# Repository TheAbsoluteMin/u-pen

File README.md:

# uPen v2
A Bluetooth smart pen that transforms handwritten notes into digital text.

## Introduction
uPen v2 (the latest version) is a complete redesign of v1. Not only were the PCB and CAD updated but the pen's purpose also changed.

With a sensor PCB and a pen ink refill in a slim case, uPen aims to bridge the gap between handwritten notes and digital notes. Especially when taking notes at school (or anywhere) by hand, it can be tedious to back up those notes online or turn them into online study aids (like Quizlet!). By seamlessly capturing, digitizing, and store handwriting strokes that can be synced online via Bluetooth, uPen v2 avoids cameras and keyboards without requiring any more effort when you write.

## Features
1. NRF52840 MCU
2. 8 megabyte SPI NOR Flash memory IC
3. Bluetooth data syncing
4. CP2102N USB-C coding
5. OLED display
6. USB-C and QVAR sensing USBLC6-2SC6 ESD protection
7. LSM6DSV16XTR IMU
8. Power timing and regulation between 5V USB-C and 3.7V LiPo battery
9. Built-in charging
10. Character recognition

## Schematics

## PCB
uPen v2 was designed with EasyEDA Pro.

### PCB Layers
Top Layer

Inner Layer 1

Inner Layer 2

Bottom Layer

### PCB Assembly
** _Please note that the SDA/SCL lines for the OLED are intentionally not connected on the PCB by default_ **
1. Solder 30 AWG wires for the OLED's SDA/SCL lines to the respective vias as marked on the PCB.
2. Solder on the OLED screen on the back of the PCB.
3. With a JST SH 1.0mm pitch connector, plug in the battery (recommended is 301020 size with 80 mAh).

## CAD Case
3D model [link](https://cad.onshape.com/documents/3034b127fe9271adab18443b/w/723b7faf19a316a6d53fa867/e/b16e1a12b2835dfae5f24d19?renderMode=0&uiState=6aef887ea209f9e2942180de).

Before, uPen v1's case was 18mm wide (that's a really big pen!), and it was designed with Autodesk Fusion.

Now, uPen v2's case is a sleek 12.5mm wide, and it was designed with Onshape.

<details>
<summary>
  <h3>Pictures</h3>
</summary>

</details>

### CAD Case Assembly
1. Attach the Button and Switch extensions on the PCB.
2. After placing the PCB inside the Bottom Case, snap the Top Case above it.
3. With the pen ink refill inside, press the Nose part onto the case. 

## How To Use
1. Ensure uPen's battery is full by charging it with a USB-C cable.
2. Begin writing with uPen v2 as if it's a normal pen.
3. You can view your notes on the screen or sync them online via Bluetooth.

## Firmware Logic: How It Works
1. uPen automatically detects when you start writing.

2. The LSM6DSV16XTR IMU captures handwriting strokes for each character that you write.

3. Each character is separated in the firmware by sensing differences in electrostatic measurements of the QVAR function of the IMU.

4. Characters are translated into text.

5. Notes are stored into the flash memory chip for long term memory.

6. Notes can be transfered via Bluetooth.

### Firmware Setup
1. Flash Nordic's software and bootloader via an SWD programmer onto the NRF52840 MCU. Instructions are found [here](https://www.nordicsemi.com/Products/nRF52840/GetStarted).
2. Upload uPen's main code [here](https://github.com/TheAbsoluteMin/u-pen/blob/main/v2_LATEST/v2_Firmware/src/main.cpp) via USB-C.

## PCB Components BOM

| Part Name | Mfr. | Description | LCSC# | Min Order Qty. | Order Qty. | Unit Price (USD) | Ext.Price (USD) | Product Link |
| :--- | :--- | :--- | :--- | :---: | :---: | :---: | :---: | :--- |
| LQP03TG2N2B02D | muRata | 450mA 2.2nH 250mΩ Thick Film Inductor 0201 Fixed Inductors RoHS | C86107 | 100 | 100 | 0.0014 | 0.14 | [Link](https://www.lcsc.com/product-detail/C86107.html?spm=wm.mxq.bom.0.xh___wm.bjg.btn.cre&lcsc_vid=EwQKVldeTwdaXlNURANeBldeElULUwdSQ1UIXlAFQAcxVlNfQ1deVFBVTlZWUzsOAxUeFF5JWA4dDxMKFgNABAsLWA%3D%3D) |
| X201632MKB4SI | YXC Crystal Oscillators | Crystal 32MHz ±10ppm 8pF SMD2016-4P | C718072 | 5 | 5 | 0.0887 | 0.44 | [Link](https://www.lcsc.com/product-detail/C718072.html?spm=wm.mxq.bom.1.xh___wm.bjg.btn.cre&lcsc_vid=EwQKVldeTwdaXlNURANeBldeElULUwdSQ1UIXlAFQAcxVlNfQ1deVFBVTlZWUzsOAxUeFF5JWA4dDxMKFgNABAsLWA%3D%3D) |
| X1A0000610008 | EPSON | Crystal 32.768kHz ±20ppm 9pF 90kΩ SMD2012-2P | C96341 | 5 | 5 | 0.1908 | 0.95 | [Link](https://www.lcsc.com/product-detail/C96341.html?spm=wm.mxq.bom.2.xh___wm.bjg.btn.cre&lcsc_vid=EwQKVldeTwdaXlNURANeBldeElULUwdSQ1UIXlAFQAcxVlNfQ1deVFBVTlZWUzsOAxUeFF5JWA4dDxMKFgNABAsLWA%3D%3D) |
| NRF52840-QFAA-F-R7 | NORDIC | IC RF TXRX 802.15.4 Bluetooth QFN-48(6x6) | C3606653 | 1 | 1 | 4.8639 | 4.86 | [Link](https://www.lcsc.com/product-detail/C3606653.html?spm=wm.mxq.bom.3.xh___wm.bjg.btn.cre&lcsc_vid=EwQKVldeTwdaXlNURANeBldeElULUwdSQ1UIXlAFQAcxVlNfQ1deVFBVTlZWUzsOAxUeFF5JWA4dDxMKFgNABAsLWA%3D%3D) |
| LQP03TN4N7H02D | muRata | 350mA 4.7nH ±3% 400mΩ 0201 Fixed Inductors RoHS | C86126 | 50 | 50 | 0.0044 | 0.22 | [Link](https://www.lcsc.com/product-detail/C86126.html?spm=wm.mxq.bom.4.xh___wm.bjg.btn.cre&lcsc_vid=EwQKVldeTwdaXlNURANeBldeElULUwdSQ1UIXlAFQAcxVlNfQ1deVFBVTlZWUzsOAxUeFF5JWA4dDxMKFgNABAsLWA%3D%3D) |
| LQG15HS15NJ02D | muRata | 450mA 15nH ±5% 320mΩ 0402 Fixed Inductors RoHS | C86059 | 20 | 20 | 0.0136 | 0.27 | [Link](https://www.lcsc.com/product-detail/C86059.html?spm=wm.mxq.bom.5.xh___wm.bjg.btn.cre&lcsc_vid=EwQKVldeTwdaXlNURANeBldeElULUwdSQ1UIXlAFQAcxVlNfQ1deVFBVTlZWUzsOAxUeFF5JWA4dDxMKFgNABAsLWA%3D%3D) |
| CC0201FRNPO9BN120 | YAGEO | 12pF ±1% 50V Ceramic Capacitor NP0 0201 | C526929 | 100 | 100 | 0.0020 | 0.20 | [Link](https://www.lcsc.com/product-detail/C526929.html?spm=wm.mxq.bom.6.xh___wm.bjg.btn.cre&lcsc_vid=EwQKVldeTwdaXlNURANeBldeElULUwdSQ1UIXlAFQAcxVlNfQ1deVFBVTlZWUzsOAxUeFF5JWA4dDxMKFgNABAsLWA%3D%3D) |
| CC0201BRNPO9BN1R0 | YAGEO | 1pF 50V Ceramic Capacitor NP0 0201 | C281747 | 100 | 100 | 0.0014 | 0.14 | [Link](https://www.lcsc.com/product-detail/C281747.html?spm=wm.mxq.bom.7.xh___wm.bjg.btn.cre&lcsc_vid=EwQKVldeTwdaXlNURANeBldeElULUwdSQ1UIXlAFQAcxVlNfQ1deVFBVTlZWUzsOAxUeFF5JWA4dDxMKFgNABAsLWA%3D%3D) |
| CC0201BRNPO9BN1R2 | YAGEO | 1.2pF 50V Ceramic Capacitor NP0 0201 | C326704 | 100 | 100 | 0.0013 | 0.13 | [Link](https://www.lcsc.com/product-detail/C326704.html?spm=wm.mxq.bom.8.xh___wm.bjg.btn.cre&lcsc_vid=EwQKVldeTwdaXlNURANeBldeElULUwdSQ1UIXlAFQAcxVlNfQ1deVFBVTlZWUzsOAxUeFF5JWA4dDxMKFgNABAsLWA%3D%3D) |
| CL03A104KP3NNNC | Samsung Electro-Mechanics | 100nF ±10% 10V Ceramic Capacitor X5R 0201 | C49062 | 100 | 100 | 0.0012 | 0.12 | [Link](https://www.lcsc.com/product-detail/C49062.html?spm=wm.mxq.bom.9.xh___wm.bjg.btn.cre&lcsc_vid=EwQKVldeTwdaXlNURANeBldeElULUwdSQ1UIXlAFQAcxVlNfQ1deVFBVTlZWUzsOAxUeFF5JWA4dDxMKFgNABAsLWA%3D%3D) |
| CC0201GRNPO9BN101 | YAGEO | 100pF ±2% 50V Ceramic Capacitor NP0 0201 | C541242 | 100 | 100 | 0.0017 | 0.17 | [Link](https://www.lcsc.com/product-detail/C541242.html?spm=wm.mxq.bom.10.xh___wm.bjg.btn.cre&lcsc_vid=EwQKVldeTwdaXlNURANeBldeElULUwdSQ1UIXlAFQAcxVlNfQ1deVFBVTlZWUzsOAxUeFF5JWA4dDxMKFgNABAsLWA%3D%3D) |
| GRM155R61A105KE15D | muRata | 1uF ±10% 10V Ceramic Capacitor X5R 0402 | C76999 | 50 | 50 | 0.0029 | 0.15 | [Link](https://www.lcsc.com/product-detail/C76999.html?spm=wm.mxq.bom.11.xh___wm.bjg.btn.cre&lcsc_vid=EwQKVldeTwdaXlNURANeBldeElULUwdSQ1UIXlAFQAcxVlNfQ1deVFBVTlZWUzsOAxUeFF5JWA4dDxMKFgNABAsLWA%3D%3D) |
| CC0201KRX5R7BB473 | YAGEO | 47nF ±10% 16V Ceramic Capacitor X5R 0201 | C505465 | 100 | 100 | 0.0021 | 0.21 | [Link](https://www.lcsc.com/product-detail/C505465.html?spm=wm.mxq.bom.12.xh___wm.bjg.btn.cre&lcsc_vid=EwQKVldeTwdaXlNURANeBldeElULUwdSQ1UIXlAFQAcxVlNfQ1deVFBVTlZWUzsOAxUeFF5JWA4dDxMKFgNABAsLWA%3D%3D) |
| AF0201FR-0710KL | YAGEO | 50mW 10kΩ 25V Thick Film Resistor ±1% ±200ppm/°C 0201 Chip Resistor - Surface Mount RoHS | C143978 | 100 | 100 | 0.0019 | 0.19 | [Link](https://www.lcsc.com/product-detail/C143978.html?spm=wm.mxq.bom.13.xh___wm.bjg.btn.cre&lcsc_vid=EwQKVldeTwdaXlNURANeBldeElULUwdSQ1UIXlAFQAcxVlNfQ1deVFBVTlZWUzsOAxUeFF5JWA4dDxMKFgNABAsLWA%3D%3D) |
| GD25Q64CWIGR | GigaDevice Semicon Beijing | 64Mbit 2.7V~3.6V 120MHz SPI WSON-8-EP(5x6) Memory RoHS | C395511 | 1 | 1 | 1.0200 | 1.02 | [Link](https://www.lcsc.com/product-detail/C395511.html?spm=wm.mxq.bom.14.xh___wm.bjg.btn.cre&lcsc_vid=EwQKVldeTwdaXlNURANeBldeElULUwdSQ1UIXlAFQAcxVlNfQ1deVFBVTlZWUzsOAxUeFF5JWA4dDxMKFgNABAsLWA%3D%3D) |
| WR02X4702FAL | Walsin | 47kΩ ±1% 50mW 0201 Thick Film Resistor | C171928 | 100 | 100 | 0.0005 | 0.05 | [Link](https://www.lcsc.com/product-detail/C171928.html?spm=wm.mxq.bom.15.xh___wm.bjg.btn.cre&lcsc_vid=EwQKVldeTwdaXlNURANeBldeElULUwdSQ1UIXlAFQAcxVlNfQ1deVFBVTlZWUzsOAxUeFF5JWA4dDxMKFgNABAsLWA%3D%3D) |
| LQM18DN100M70L | muRata | 300mA 10uH ±20% 100mA 1.365Ω 0603 Fixed Inductors RoHS | C713281 | 5 | 5 | 0.0850 | 0.43 | [Link](https://www.lcsc.com/product-detail/C713281.html?spm=wm.mxq.bom.16.xh___wm.bjg.btn.cre&lcsc_vid=EwQKVldeTwdaXlNURANeBldeElULUwdSQ1UIXlAFQAcxVlNfQ1deVFBVTlZWUzsOAxUeFF5JWA4dDxMKFgNABAsLWA%3D%3D) |
| EVQP2P02W | PANASONIC | Tactile Switch SPST 1N 2.5mm J-Lead 4.7mm x 3.5mm Surface Mount | C512395 | 1 | 2 | 0.3696 | 0.74 | [Link](https://www.lcsc.com/product-detail/C512395.html?spm=wm.mxq.bom.17.xh___wm.bjg.btn.cre&lcsc_vid=EwQKVldeTwdaXlNURANeBldeElULUwdSQ1UIXlAFQAcxVlNfQ1deVFBVTlZWUzsOAxUeFF5JWA4dDxMKFgNABAsLWA%3D%3D) |
| AMCA31-2R450G-S1F-T3 | ABRACON | Surface Mount WLAN / Bluetooth Chip Antenna | C3283994 | 5 | 5 | 0.2603 | 1.30 | [Link](https://www.lcsc.com/product-detail/C3283994.html?spm=wm.mxq.bom.19.xh___wm.bjg.btn.cre&lcsc_vid=EwQKVldeTwdaXlNURANeBldeElULUwdSQ1UIXlAFQAcxVlNfQ1deVFBVTlZWUzsOAxUeFF5JWA4dDxMKFgNABAsLWA%3D%3D) |
| CC0402CRNPO9BN1R5 | YAGEO | 1.5pF 50V Ceramic Capacitor NP0 0402 | C189471 | 100 | 100 | 0.0010 | 0.10 | [Link](https://www.lcsc.com/product-detail/C189471.html?spm=wm.mxq.bom.20.xh___wm.bjg.btn.cre&lcsc_vid=EwQKVldeTwdaXlNURANeBldeElULUwdSQ1UIXlAFQAcxVlNfQ1deVFBVTlZWUzsOAxUeFF5JWA4dDxMKFgNABAsLWA%3D%3D) |
| MLG1005S3N9BT000 | TDK | 700mA 3.9nH 110mΩ Multilayer inductor 0402 Fixed Inductors RoHS | C76775 | 10 | 10 | 0.0065 | 0.07 | [Link](https://www.lcsc.com/product-detail/C76775.html?spm=wm.mxq.bom.21.xh___wm.bjg.btn.cre&lcsc_vid=EwQKVldeTwdaXlNURANeBldeElULUwdSQ1UIXlAFQAcxVlNfQ1deVFBVTlZWUzsOAxUeFF5JWA4dDxMKFgNABAsLWA%3D%3D) |
| CP2102N-A02-GQFN20R | SILICON LABS | USB to UART 3Mbps QFN-20-EP(3x3) Controllers RoHS | C969913 | 1 | 1 | 1.4298 | 1.43 | [Link](https://www.lcsc.com/product-detail/C969913.html?spm=wm.mxq.bom.22.xh___wm.bjg.btn.cre&lcsc_vid=EwQKVldeTwdaXlNURANeBldeElULUwdSQ1UIXlAFQAcxVlNfQ1deVFBVTlZWUzsOAxUeFF5JWA4dDxMKFgNABAsLWA%3D%3D) |
| TYPE-C16PIN | SHOU HAN | USB-C (USB TYPE-C) Receptacle Connector 16 Position Surface Mount, Right Angle | C393939 | 10 | 10 | 0.0595 | 0.60 | [Link](https://www.lcsc.com/product-detail/C393939.html?spm=wm.mxq.bom.23.xh___wm.bjg.btn.cre&lcsc_vid=EwQKVldeTwdaXlNURANeBldeElULUwdSQ1UIXlAFQAcxVlNfQ1deVFBVTlZWUzsOAxUeFF5JWA4dDxMKFgNABAsLWA%3D%3D) |
| XC6206P332MR-G | TOREX | 3.3V Positive Fixed SOT-23-3L Voltage Regulators - Linear, Low Drop Out (LDO) Regulators RoHS | C5446 | 5 | 5 | 0.1342 | 0.67 | [Link](https://www.lcsc.com/product-detail/C5446.html?spm=wm.mxq.bom.24.xh___wm.bjg.btn.cre&lcsc_vid=EwQKVldeTwdaXlNURANeBldeElULUwdSQ1UIXlAFQAcxVlNfQ1deVFBVTlZWUzsOAxUeFF5JWA4dDxMKFgNABAsLWA%3D%3D) |
| AF0201FR-075K1L | YAGEO | 50mW 5.1kΩ 25V Thick Film Resistor ±1% ±200ppm/°C 0201 Chip Resistor - Surface Mount RoHS | C143995 | 100 | 100 | 0.0019 | 0.19 | [Link](https://www.lcsc.com/product-detail/C143995.html?spm=wm.mxq.bom.25.xh___wm.bjg.btn.cre&lcsc_vid=EwQKVldeTwdaXlNURANeBldeElULUwdSQ1UIXlAFQAcxVlNfQ1deVFBVTlZWUzsOAxUeFF5JWA4dDxMKFgNABAsLWA%3D%3D) |
| CGA0402X5R475K160GT | HRE | 4.7uF X5R ±10% 16V 0402 Ceramic Capacitors | C52037851 | 20 | 20 | 0.0144 | 0.29 | [Link](https://www.lcsc.com/product-detail/C52037851.html?spm=wm.mxq.bom.26.xh___wm.bjg.btn.cre&lcsc_vid=EwQKVldeTwdaXlNURANeBldeElULUwdSQ1UIXlAFQAcxVlNfQ1deVFBVTlZWUzsOAxUeFF5JWA4dDxMKFgNABAsLWA%3D%3D) |
| USBLC6-2SC6 | ST | 17VC Clamp 5A Ipp ESD DIODE SOT-23-6L | C7519 | 5 | 5 | 0.1391 | 0.70 | [Link](https://www.lcsc.com/product-detail/C7519.html?spm=wm.mxq.bom.27.xh___wm.bjg.btn.cre&lcsc_vid=EwQKVldeTwdaXlNURANeBldeElULUwdSQ1UIXlAFQAcxVlNfQ1deVFBVTlZWUzsOAxUeFF5JWA4dDxMKFgNABAsLWA%3D%3D) |
| RC0201FR-0722K1L | YAGEO | 50mW 22.1kΩ 25V Thick Film Resistor ±1% ±200ppm/°C 0201 Chip Resistor - Surface Mount RoHS | C142019 | 100 | 100 | 0.0005 | 0.05 | [Link](https://www.lcsc.com/product-detail/C142019.html?spm=wm.mxq.bom.28.xh___wm.bjg.btn.cre&lcsc_vid=EwQKVldeTwdaXlNURANeBldeElULUwdSQ1UIXlAFQAcxVlNfQ1deVFBVTlZWUzsOAxUeFF5JWA4dDxMKFgNABAsLWA%3D%3D) |
| 0201WMF4752TEE | UNI-ROYAL | 47.5kΩ ±1% 50mW 0201 Thick Film Resistor | C473579 | 100 | 100 | 0.0005 | 0.05 | [Link](https://www.lcsc.com/product-detail/C473579.html?spm=wm.mxq.bom.29.xh___wm.bjg.btn.cre&lcsc_vid=EwQKVldeTwdaXlNURANeBldeElULUwdSQ1UIXlAFQAcxVlNfQ1deVFBVTlZWUzsOAxUeFF5JWA4dDxMKFgNABAsLWA%3D%3D) |
| RC0201FR-0727KL | YAGEO | 27kΩ 50mW 25V Thick Film Resistor ±1% ±200ppm/°C 0201 Chip Resistor - Surface Mount RoHS | C273283 | 100 | 100 | 0.0005 | 0.05 | [Link](https://www.lcsc.com/product-detail/C273283.html?spm=wm.mxq.bom.30.xh___wm.bjg.btn.cre&lcsc_vid=EwQKVldeTwdaXlNURANeBldeElULUwdSQ1UIXlAFQAcxVlNfQ1deVFBVTlZWUzsOAxUeFF5JWA4dDxMKFgNABAsLWA%3D%3D) |
| RC0201JR-071KL | YAGEO | 50mW 1kΩ 25V Thick Film Resistor ±5% ±200ppm/°C 0201 Chip Resistor - Surface Mount RoHS | C131396 | 100 | 100 | 0.0004 | 0.04 | [Link](https://www.lcsc.com/product-detail/C131396.html?spm=wm.mxq.bom.31.xh___wm.bjg.btn.cre&lcsc_vid=EwQKVldeTwdaXlNURANeBldeElULUwdSQ1UIXlAFQAcxVlNfQ1deVFBVTlZWUzsOAxUeFF5JWA4dDxMKFgNABAsLWA%3D%3D) |
| RC0201FR-07100KL | YAGEO | 50mW 100kΩ 25V Thick Film Resistor ±1% ±200ppm/°C 0201 Chip Resistor - Surface Mount RoHS | C106224 | 100 | 100 | 0.0006 | 0.06 | [Link](https://www.lcsc.com/product-detail/C106224.html?spm=wm.mxq.bom.32.xh___wm.bjg.btn.cre&lcsc_vid=EwQKVldeTwdaXlNURANeBldeElULUwdSQ1UIXlAFQAcxVlNfQ1deVFBVTlZWUzsOAxUeFF5JWA4dDxMKFgNABAsLWA%3D%3D) |
| SH1.0mm-2P-WT | LXWCONN | Surface Mount, Right Angle 1mm 1A SH 50V -25°C~+85°C Tin 2P 2 1 1x2P SMD,P=1mm,Surface Mount,Right Angle Headers, Male Pins | C53055318 | 20 | 20 | 0.0225 | 0.45 | [Link](https://www.lcsc.com/product-detail/C53055318.html?spm=wm.mxq.bom.33.xh___wm.bjg.btn.cre&lcsc_vid=EwQKVldeTwdaXlNURANeBldeElULUwdSQ1UIXlAFQAcxVlNfQ1deVFBVTlZWUzsOAxUeFF5JWA4dDxMKFgNABAsLWA%3D%3D) |
| MCP73831T-2ATI/OT | MICROCHIP | 3.75V~6V 1 Lithium Battery 550mA SOT-23-5 Battery Chargers RoHS | C14879 | 1 | 1 | 0.8160 | 0.82 | [Link](https://www.lcsc.com/product-detail/C14879.html?spm=wm.mxq.bom.34.xh___wm.bjg.btn.cre&lcsc_vid=EwQKVldeTwdaXlNURANeBldeElULUwdSQ1UIXlAFQAcxVlNfQ1deVFBVTlZWUzsOAxUeFF5JWA4dDxMKFgNABAsLWA%3D%3D) |
| TPS2116DRLR | TI | 2 Channel 2.5A SOT-583 | C3235557 | 1 | 1 | 0.3234 | 0.32 | [Link](https://www.lcsc.com/product-detail/C3235557.html?spm=wm.mxq.bom.35.xh___wm.bjg.btn.cre&lcsc_vid=EwQKVldeTwdaXlNURANeBldeElULUwdSQ1UIXlAFQAcxVlNfQ1deVFBVTlZWUzsOAxUeFF5JWA4dDxMKFgNABAsLWA%3D%3D) |
| RC0201FR-07620RL | YAGEO | 620Ω 50mW 25V Thick Film Resistor ±1% ±200ppm/°C 0201 Chip Resistor - Surface Mount RoHS | C295811 | 100 | 100 | 0.0005 | 0.05 | [Link](https://www.lcsc.com/product-detail/C295811.html?spm=wm.mxq.bom.36.xh___wm.bjg.btn.cre&lcsc_vid=EwQKVldeTwdaXlNURANeBldeElULUwdSQ1UIXlAFQAcxVlNfQ1deVFBVTlZWUzsOAxUeFF5JWA4dDxMKFgNABAsLWA%3D%3D) |
| KT-0603YG | Hubei KENTO Elec | Yellow Green LED Indication - Discrete 2V~2.2V 0603 | C2289 | 50 | 50 | 0.0066 | 0.33 | [Link](https://www.lcsc.com/product-detail/C2289.html?spm=wm.mxq.bom.37.xh___wm.bjg.btn.cre&lcsc_vid=EwQKVldeTwdaXlNURANeBldeElULUwdSQ1UIXlAFQAcxVlNfQ1deVFBVTlZWUzsOAxUeFF5JWA4dDxMKFgNABAsLWA%3D%3D) |
| HX MSS12C02-BB2.0 | hanxia | Slide Switch SPDT 100mA @ 12V Surface Mount Rectangular Columnar 6.65mm | C25168817 | 5 | 5 | 0.0853 | 0.43 | [Link](https://www.lcsc.com/product-detail/C25168817.html?spm=wm.mxq.bom.38.xh___wm.bjg.btn.cre&lcsc_vid=EwQKVldeTwdaXlNURANeBldeElULUwdSQ1UIXlAFQAcxVlNfQ1deVFBVTlZWUzsOAxUeFF5JWA4dDxMKFgNABAsLWA%3D%3D) |
| LSM6DSV16XTR | ST | LGA-14(2.5x3) IMUs (Inertial Measurement Units) RoHS | C5267406 | 1 | 1 | 2.4405 | 2.44 | [Link](https://www.lcsc.com/product-detail/C5267406.html?spm=wm.mxq.bom.39.xh___wm.bjg.btn.cre&lcsc_vid=EwQKVldeTwdaXlNURANeBldeElULUwdSQ1UIXlAFQAcxVlNfQ1deVFBVTlZWUzsOAxUeFF5JWA4dDxMKFgNABAsLWA%3D%3D) |
| RC0201FR-072K2L | YAGEO | 50mW 2.2kΩ 25V Thick Film Resistor ±1% ±200ppm/°C 0201 Chip Resistor - Surface Mount RoHS | C142018 | 100 | 100 | 0.0005 | 0.05 | [Link](https://www.lcsc.com/product-detail/C142018.html?spm=wm.mxq.bom.40.xh___wm.bjg.btn.cre&lcsc_vid=EwQKVldeTwdaXlNURANeBldeElULUwdSQ1UIXlAFQAcxVlNfQ1deVFBVTlZWUzsOAxUeFF5JWA4dDxMKFgNABAsLWA%3D%3D) |
| X087-2832TSWIG02-H14 | Wisevision | 0.87 128x32 SSD1312 chip I2C LCD, OLED, Graphic RoHS | C18723015 | 1 | 1 | 1.4902 | 1.49 | [Link](https://www.lcsc.com/product-detail/C18723015.html?spm=wm.mxq.bom.41.xh___wm.bjg.btn.cre&lcsc_vid=EwQKVldeTwdaXlNURANeBldeElULUwdSQ1UIXlAFQAcxVlNfQ1deVFBVTlZWUzsOAxUeFF5JWA4dDxMKFgNABAsLWA%3D%3D) |
| CC0603KRX7R7BB225 | YAGEO | 2.2uF ±10% 16V Ceramic Capacitor X7R 0603 | C914769 | 10 | 10 | 0.0381 | 0.38 | [Link](https://www.lcsc.com/product-detail/C914769.html?spm=wm.mxq.bom.42.xh___wm.bjg.btn.cre&lcsc_vid=EwQKVldeTwdaXlNURANeBldeElULUwdSQ1UIXlAFQAcxVlNfQ1deVFBVTlZWUzsOAxUeFF5JWA4dDxMKFgNABAsLWA%3D%3D) |
| CGA0603X7R475K160JT | HRE | 4.7uF ±10% 16V Ceramic Capacitor X7R 0603 | C22399629 | 20 | 20 | 0.0174 | 0.35 | [Link](https://www.lcsc.com/product-detail/C22399629.html?spm=wm.mxq.bom.43.xh___wm.bjg.btn.cre&lcsc_vid=EwQKVldeTwdaXlNURANeBldeElULUwdSQ1UIXlAFQAcxVlNfQ1deVFBVTlZWUzsOAxUeFF5JWA4dDxMKFgNABAsLWA%3D%3D) |
| TCC0201X7R104K160ZT | CCTC | 100nF ±10% 16V Ceramic Capacitor X7R 0201 | C18164586 | 50 | 50 | 0.0017 | 0.09 | [Link](https://www.lcsc.com/product-detail/C18164586.html?spm=wm.mxq.bom.44.xh___wm.bjg.btn.cre&lcsc_vid=EwQKVldeTwdaXlNURANeBldeElULUwdSQ1UIXlAFQAcxVlNfQ1deVFBVTlZWUzsOAxUeFF5JWA4dDxMKFgNABAsLWA%3D%3D) |
| CC0603KRX7R7BB105 | YAGEO | 1uF ±10% 16V Ceramic Capacitor X7R 0603 | C106248 | 50 | 50 | 0.0039 | 0.20 | [Link](https://www.lcsc.com/product-detail/C106248.html?spm=wm.mxq.bom.45.xh___wm.bjg.btn.cre&lcsc_vid=EwQKVldeTwdaXlNURANeBldeElULUwdSQ1UIXlAFQAcxVlNfQ1deVFBVTlZWUzsOAxUeFF5JWA4dDxMKFgNABAsLWA%3D%3D) |
| RC0201FR-07560KL | YAGEO | 50mW 560kΩ 25V Thick Film Resistor ±1% ±200ppm/°C 0201 Chip Resistor - Surface Mount RoHS | C295807 | 100 | 100 | 0.0005 | 0.05 | [Link](https://www.lcsc.com/product-detail/C295807.html?spm=wm.mxq.bom.46.xh___wm.bjg.btn.cre&lcsc_vid=EwQKVldeTwdaXlNURANeBldeElULUwdSQ1UIXlAFQAcxVlNfQ1deVFBVTlZWUzsOAxUeFF5JWA4dDxMKFgNABAsLWA%3D%3D) |
| FDN338P | onsemi | P-Channel 20V 1.6A 0.5W Surface Mount SOT-23 | C24855 | 5 | 5 | 0.1807 | 0.90 | [Link](https://www.lcsc.com/product-detail/C24855.html?spm=wm.mxq.bom.47.xh___wm.bjg.btn.cre&lcsc_vid=EwQKVldeTwdaXlNURANeBldeElULUwdSQ1UIXlAFQAcxVlNfQ1deVFBVTlZWUzsOAxUeFF5JWA4dDxMKFgNABAsLWA%3D%3D) |
| FDN335N | onsemi | N-Channel 20V 1.7A 0.5W Surface Mount SOT-23-3 | C241804 | 5 | 5 | 0.1477 | 0.74 | [Link](https://www.lcsc.com/product-detail/C241804.html?spm=wm.mxq.bom.48.xh___wm.bjg.btn.cre&lcsc_vid=EwQKVldeTwdaXlNURANeBldeElULUwdSQ1UIXlAFQAcxVlNfQ1deVFBVTlZWUzsOAxUeFF5JWA4dDxMKFgNABAsLWA%3D%3D) |
| RC0201FR-071ML | YAGEO | 50mW 1MΩ 25V Thick Film Resistor ±1% ±200ppm/°C 0201 Chip Resistor - Surface Mount RoHS | C295786 | 100 | 100 | 0.0005 | 0.05 | [Link](https://www.lcsc.com/product-detail/C295786.html?spm=wm.mxq.bom.49.xh___wm.bjg.btn.cre&lcsc_vid=EwQKVldeTwdaXlNURANeBldeElULUwdSQ1UIXlAFQAcxVlNfQ1deVFBVTlZWUzsOAxUeFF5JWA4dDxMKFgNABAsLWA%3D%3D) |
| Total | | Total is included in uPen PCBA | | | | (USD) | $25.17 | Without Shipping |

## Full BOM

| Part Name | Quantity | Total Price | Where to Buy |
| :--- | :---: | :---: | :--- |
| uPen PCB | 5 | 69.56 | [JLCPCB](https://jlcpcb.com/) |
| uPen PCBA | 2 | 181.85 | [JLCPCB](https://jlcpcb.com/) |
| OLED Screen | 2 | 3.64 | [LCSC](https://www.lcsc.com/product-detail/C18723015.html?s_z=n_q_C18723015&globalKeyword=C18723015) |
| 30 AWG 0.5MM PCB Flying Jumper Wire | 1 | 7.00 | [AliExpress](https://www.aliexpress.us/item/2255800481153606.html?spm=a2g0o.productlist.main.1.5b8c52c6dqhfpX&algo_pvid=c0db41cf-f68a-49f3-b0cd-bbb869e4a1ec&algo_exp_id=c0db41cf-f68a-49f3-b0cd-bbb869e4a1ec-0&pdp_ext_f=%7B%22order%22%3A%22887%22%2C%22eval%22%3A%221%22%2C%22fromPage%22%3A%22search%22%7D&pdp_npi=6%40dis%21USD%217.00%211.09%21%21%217.00%211.09%21%40210327b017942627382282212e0e79%2110000005571941385%21sea%21US%210%21ABX%211%210%21n_tag%3A-29910%3Bd%3Aa3d7507d%3Bm03_new_user%3A-29895%3BpisId%3A5000000218165391&curPageLogUid=KjZBONr446qX&utparam-url=scene%3Asearch%7Cquery_from%3A%7Cx_object_id%3A4000667468358%7C_p_origin_prod%3A) |
| 301020 LiPo Batteries | 1 | 10.11 | [AliExpress](https://www.aliexpress.us/item/2251832810583728.html?spm=a2g0o.productlist.main.9.461bE4UAE4UArO&algo_pvid=3fd1e6d2-fe38-4eb0-b39f-49b563c3360b&algo_exp_id=3fd1e6d2-fe38-4eb0-b39f-49b563c3360b-8&pdp_ext_f=%7B%22order%22%3A%2235%22%2C%22eval%22%3A%221%22%2C%22fromPage%22%3A%22search%22%7D&pdp_npi=6%40dis%21USD%2111.90%2110.00%21%21%2111.90%2110.00%21%402101d9ef17894343212786799e0d3e%2112000024080089254%21sea%21US%210%21ABX%211%210%21n_tag%3A-29910%3Bd%3A748d72d8%3Bm03_new_user%3A-29895&curPageLogUid=2JfzQbrL5XBB&utparam-url=scene%3Asearch%7Cquery_from%3A%7Cx_object_id%3A32996898480%7C_p_origin_prod%3A) |
| JST SH 1.0mm 2 Pin Cable | 1 | 3.69 | [AliExpress](https://www.aliexpress.us/item/3256809955750969.html?spm=a2g0o.productlist.main.3.62173c93cfTMBm&algo_pvid=2fcf1894-dfaa-4ec2-b01e-256d85639e75&algo_exp_id=2fcf1894-dfaa-4ec2-b01e-256d85639e75-2&pdp_ext_f=%7B%22order%22%3A%221818%22%2C%22eval%22%3A%221%22%2C%22fromPage%22%3A%22search%22%7D&pdp_npi=6%40dis%21USD%213.69%211.09%21%21%2124.51%217.27%21%402101e80b17942634635358014e108a%2112000051297274513%21sea%21US%210%21ABX%211%210%21n_tag%3A-29910%3Bd%3A50adb272%3Bm03_new_user%3A-29895%3BpisId%3A5000000218165389&curPageLogUid=ZEVk2uUcjnsi&utparam-url=scene%3Asearch%7Cquery_from%3A%7Cx_object_id%3A1005010142065721%7C_p_origin_prod%3A) |
| OB-ARM Emulator (SWD) Debugger Programmer | 1 | 2.39 | [AliExpress](https://www.aliexpress.us/item/3256804889623613.html?spm=a2g0o.productlist.main.5.42947b73SrJzEG&algo_pvid=e1381424-0565-4f4a-8087-da6705d4fb17&algo_exp_id=e1381424-0565-4f4a-8087-da6705d4fb17-4&pdp_ext_f=%7B%22order%22%3A%22133%22%2C%22eval%22%3A%221%22%2C%22fromPage%22%3A%22search%22%7D&pdp_npi=6%40dis%21USD%212.39%212.22%21%21%212.39%212.22%21%402101ca9517942735271525494e0e07%2112000034785341692%21sea%21US%210%21ABX%211%210%21n_tag%3A-29910%3Bd%3A50adb272%3Bm03_new_user%3A-29895%3BpisId%3A5000000220758679&curPageLogUid=V1MZeZdXsAxP&utparam-url=scene%3Asearch%7Cquery_from%3A%7Cx_object_id%3A1005005075938365%7C_p_origin_prod%3A) |
| uPen 3D Printed Parts | 1 | 1.00 | [Filament from local 3D printer](https://github.com/TheAbsoluteMin/u-pen/tree/main/v2_LATEST/v2_3D_Models/3D_Printing) |
| Total | (USD) | $279.24 | Without Shipping |

## Credits
Thank you so much for generously funding and supporting the creation of uPen v2:
- Hack Club
- EasyEDA

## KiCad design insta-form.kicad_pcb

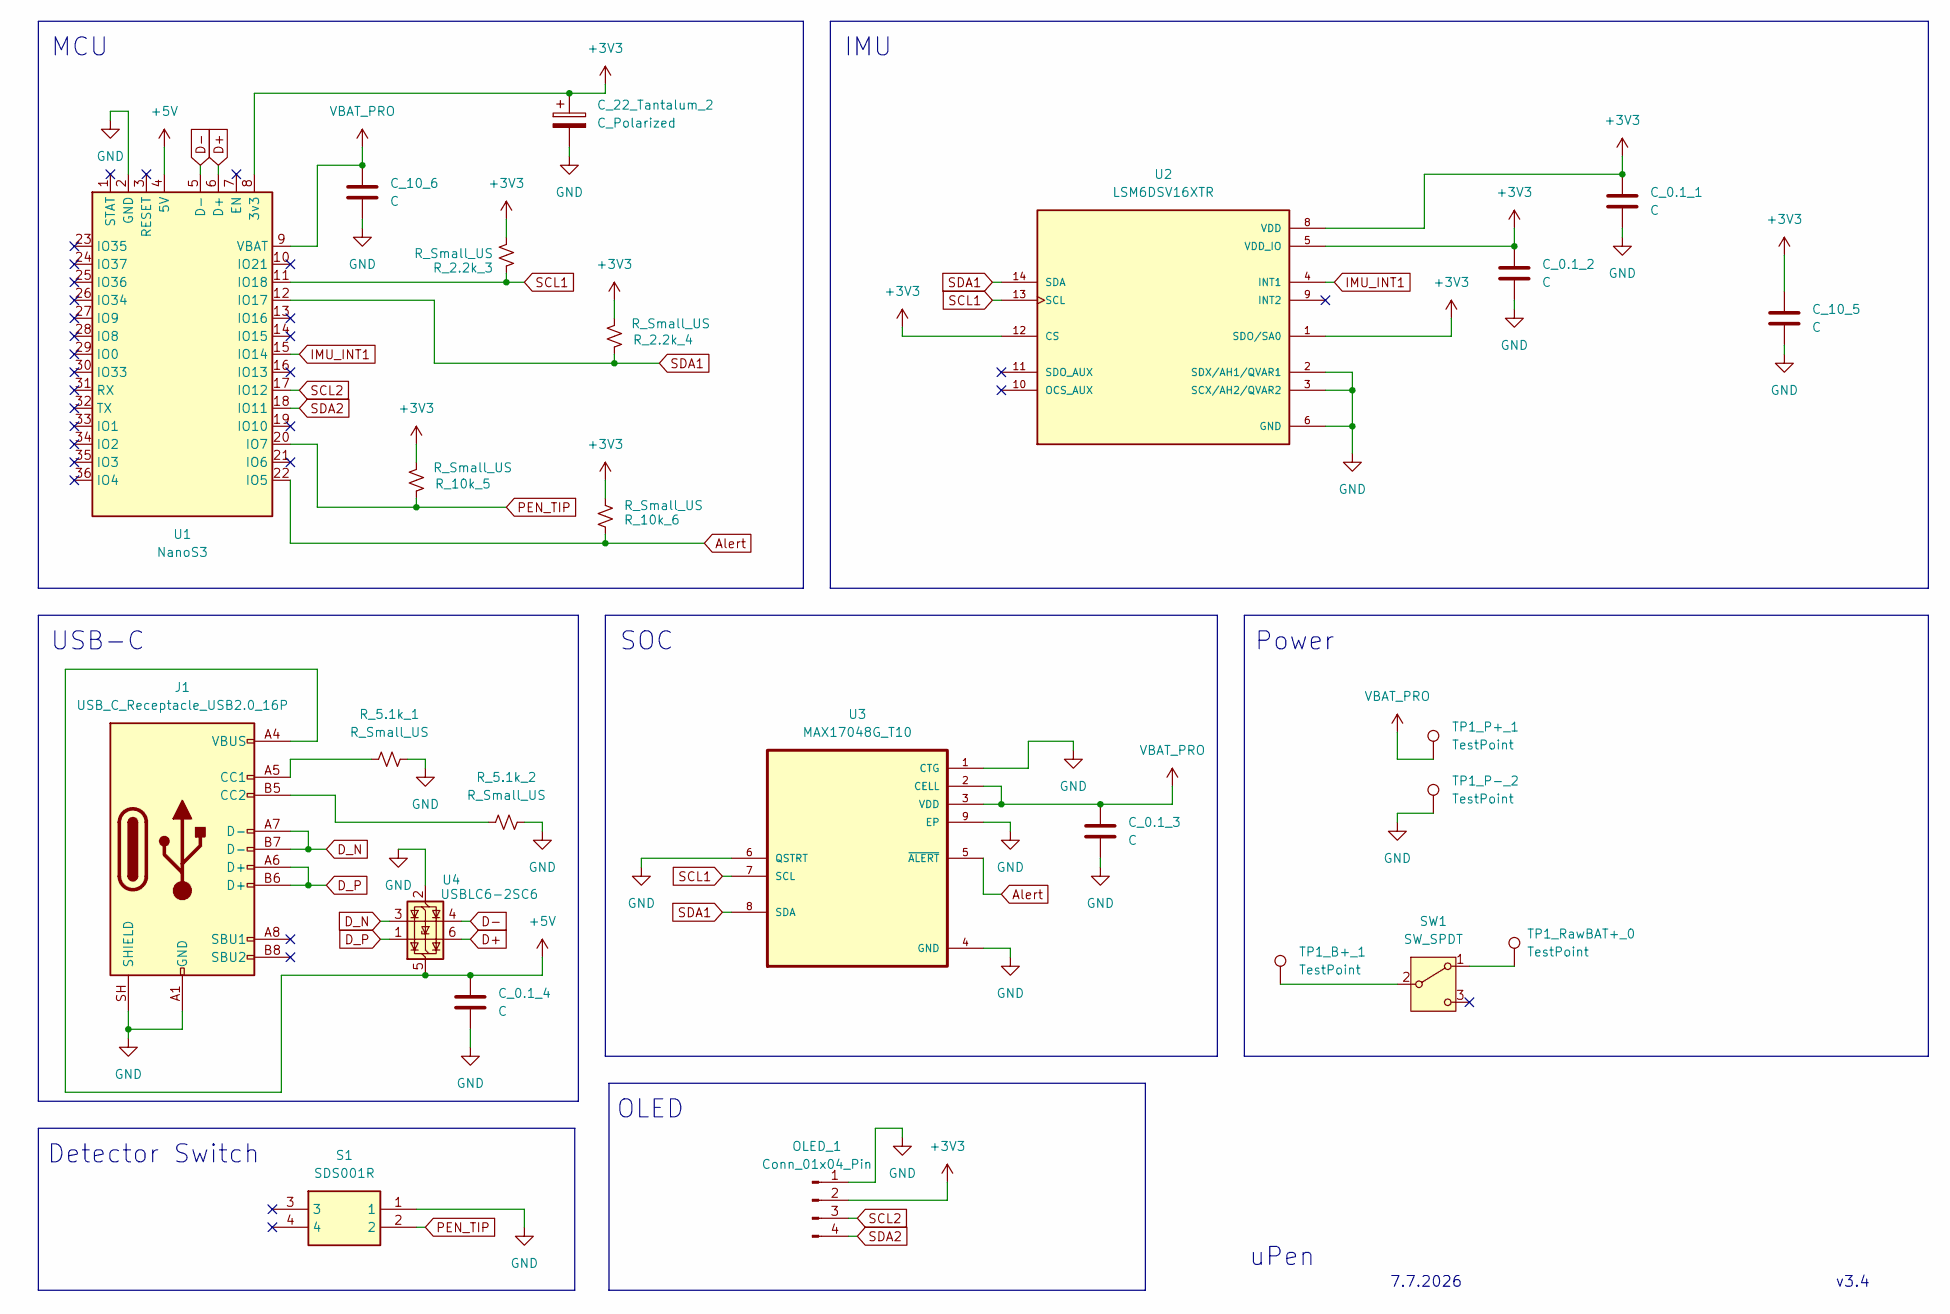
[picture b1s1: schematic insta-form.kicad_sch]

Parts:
C_0.1_1, C_0.1_2, C_0.1_3, C_0.1_4: C; C_0402_1005Metric
C_10_5, C_10_6: C; C_0603_1608Metric
C_22_Tantalum_2: C_Polarized; CP_EIA-3528-12_Kemet-T
J1: USB_C_Receptacle_USB2.0_16P; USB_C_Receptacle_XKB_U262-16XN-4BVC11
OLED_1: Conn_01x04_Pin; PinHeader_1x04_P2.54mm_Vertical
R_2.2k_3, R_2.2k_4, R_5.1k_1, R_5.1k_2, R_10k_5, R_10k_6: R_Small_US; R_0402_1005Metric
S1: SDS001R; Manufacturer_Part_Number SDS001R
SW1: SW_SPDT; SW_SPDT_PCM12
TP1_B+_1, TP1_P+_1, TP1_P-_2, TP1_RawBAT+_0: TestPoint; PinHeader_1x01_P2.54mm_Vertical
U1: NanoS3
U2: LSM6DSV16XTR; XDCR_LSM6DSV16XTR; PARTREV 4
U3: MAX17048G_T10; SON50P200X200X80-9N
U4: USBLC6-2SC6; SOT-23-6

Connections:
+3V3: C_0.1_1.1, C_0.1_2.1, C_10_5.1, C_22_Tantalum_2.1, OLED_1.2, R_2.2k_3.2, R_2.2k_4.2, R_10k_5.2, R_10k_6.1, U1.8 (3v3), U2.1 (SDO/SA0), U2.5 (VDD_IO), U2.8 (VDD), U2.12 (CS)
+5V: C_0.1_4.1, J1.A4 (VBUS), J1.A9 (VBUS), J1.B4 (VBUS), J1.B9 (VBUS), U1.4 (5V), U4.5 (VBUS)
Alert: R_10k_6.2, U1.22 (IO5), U3.5 (~ALERT)
D+: U1.6 (D+), U4.6 (I/O1)
D-: U1.5 (D-), U4.4 (I/O2)
D_N: J1.A7 (D-), J1.B7 (D-), U4.3 (I/O2)
D_P: J1.A6 (D+), J1.B6 (D+), U4.1 (I/O1)
GND: C_0.1_1.2, C_0.1_2.2, C_0.1_3.2, C_0.1_4.2, C_10_5.2, C_10_6.2, C_22_Tantalum_2.2, J1.A1 (GND), J1.A12 (GND), J1.B1 (GND), J1.B12 (GND), J1.SH (SHIELD), OLED_1.1, R_5.1k_1.1, R_5.1k_2.1, S1.1, TP1_P-_2.1 (1_1), U1.2 (GND), U1.EXP, U2.2 (SDX/AH1/QVAR1), U2.3 (SCX/AH2/QVAR2), U2.6 (GND), U2.7 (GND), U3.1 (CTG), U3.4 (GND), U3.6 (QSTRT), U3.9 (EP), U4.2 (GND)
IMU_INT1: U1.15 (IO14), U2.4 (INT1)
unnamed: J1.A5 (CC1), R_5.1k_1.2
unnamed: J1.B5 (CC2), R_5.1k_2.2
unnamed: SW1.1 (A), TP1_RawBAT+_0.1 (1_1)
unnamed: SW1.2 (B), TP1_B+_1.1 (1_1)
PEN_TIP: R_10k_5.1, S1.2, U1.20 (IO7)
SCL1: R_2.2k_3.1, U1.11 (IO18), U2.13 (SCL), U3.7 (SCL)
SCL2: OLED_1.3, U1.17 (IO12)
SDA1: R_2.2k_4.1, U1.12 (IO17), U2.14 (SDA), U3.8 (SDA)
SDA2: OLED_1.4, U1.18 (IO11)
VBAT_PRO: C_0.1_3.1, C_10_6.1, TP1_P+_1.1 (1_1), U1.9 (VBAT), U3.2 (CELL), U3.3 (VDD)

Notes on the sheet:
OLED
USB-C
Detector Switch
MCU
v3.4
uPen
7.7.2026
IMU
Power
SOC

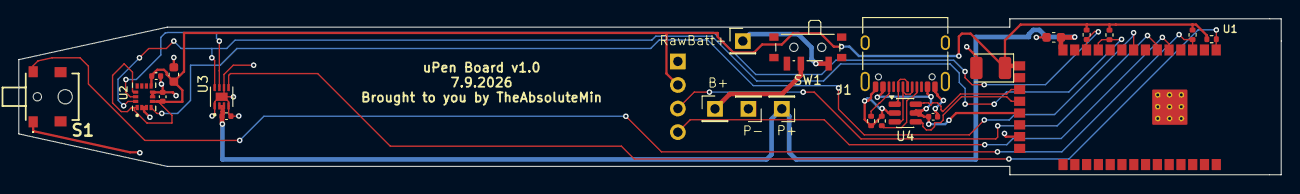
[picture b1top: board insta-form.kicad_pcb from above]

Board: 4 copper layers, 136.0 x 16.8 mm, 25 parts (1 on the bottom side), 19 nets.

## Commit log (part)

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2026-06-22 Create JOURNAL.md 1
2026-06-22 Update README.md title
2026-06-30 Update JOURNAL.md 2
